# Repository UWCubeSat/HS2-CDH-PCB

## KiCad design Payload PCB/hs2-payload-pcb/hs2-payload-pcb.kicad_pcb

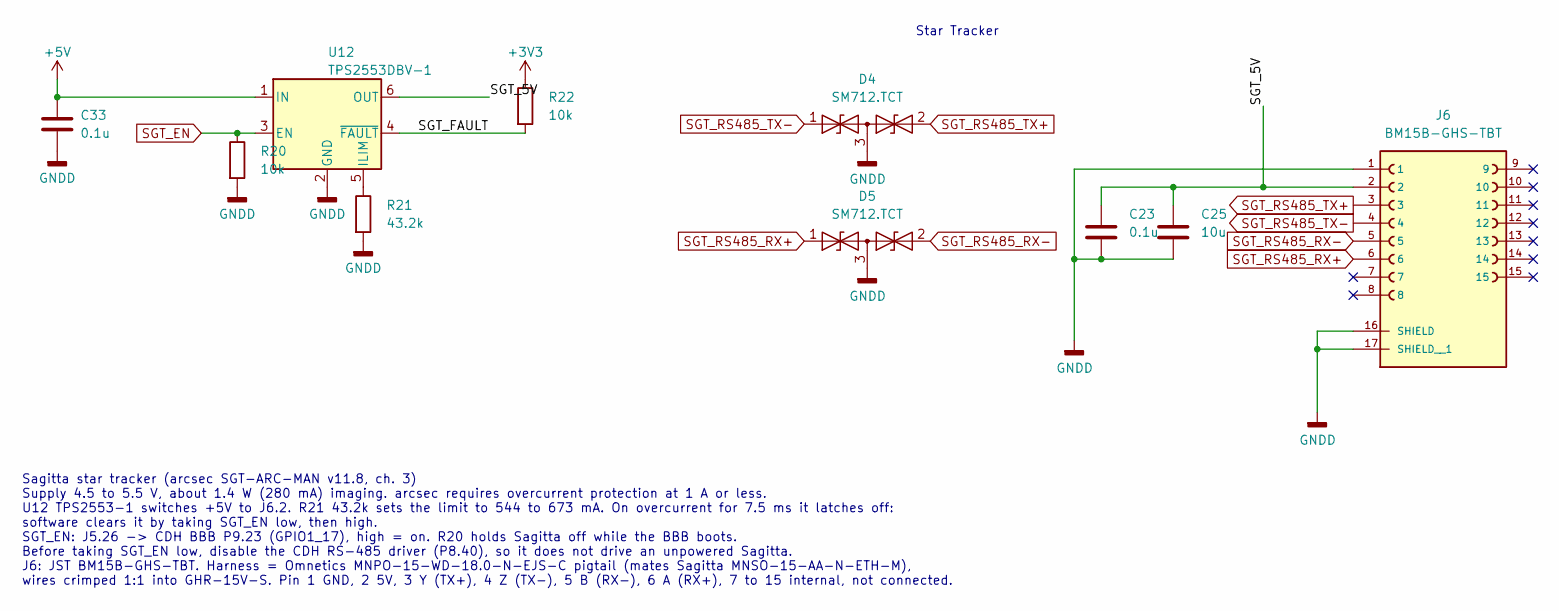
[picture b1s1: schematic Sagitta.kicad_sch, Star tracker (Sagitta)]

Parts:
C23, C33: 0.1u; C_0603_1608Metric
C25: 10u; C_0603_1608Metric
D4, D5: SM712.TCT; SOT-23; MPN SM712.TCT
J6: BM15B-GHS-TBT; BM15BGHSTBTLFSN; PARTREV B
R20, R22: 10k; R_0603_1608Metric
R21: 43.2k; R_0603_1608Metric
U12: TPS2553DBV-1; SOT-23-6; MPN TPS2553DBVR-1

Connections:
+3V3: R22.1; also elsewhere on the board
+5V: C33.1, U12.1 (IN); also elsewhere on the board
/Sagitta/SGT_5V: C23.1, C25.1, J6.2, U12.6 (OUT)
/Sagitta/SGT_FAULT: R22.2, U12.4 (~FAULT)
GNDD: C23.2, C25.2, C33.2, D4.3 (common), D5.3 (common), J6.1, J6.16 (SHIELD), J6.17 (SHIELD__1), R20.2, R21.2, U12.2 (GND); also elsewhere on the board
unnamed: R21.1, U12.5 (ILIM)
SGT_EN: R20.1, U12.3 (EN); also elsewhere on the board
SGT_RS485_RX+: D5.1 (A1), J6.6; also elsewhere on the board
SGT_RS485_RX-: D5.2 (A2), J6.5; also elsewhere on the board
SGT_RS485_TX+: D4.2 (A2), J6.3; also elsewhere on the board
SGT_RS485_TX-: D4.1 (A1), J6.4; also elsewhere on the board

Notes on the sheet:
Star Tracker
Sagitta star tracker (arcsec SGT-ARC-MAN v11.8, ch. 3) Supply 4.5 to 5.5 V, about 1.4 W (280 mA) imaging. arcsec requires overcurrent protection at 1 A or less. U12 TPS2553-1 switches +5V to J6.2. R21 43.2k sets the limit to 544 to 673 mA. On overcurrent for 7.5 ms it latches off: software clears i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

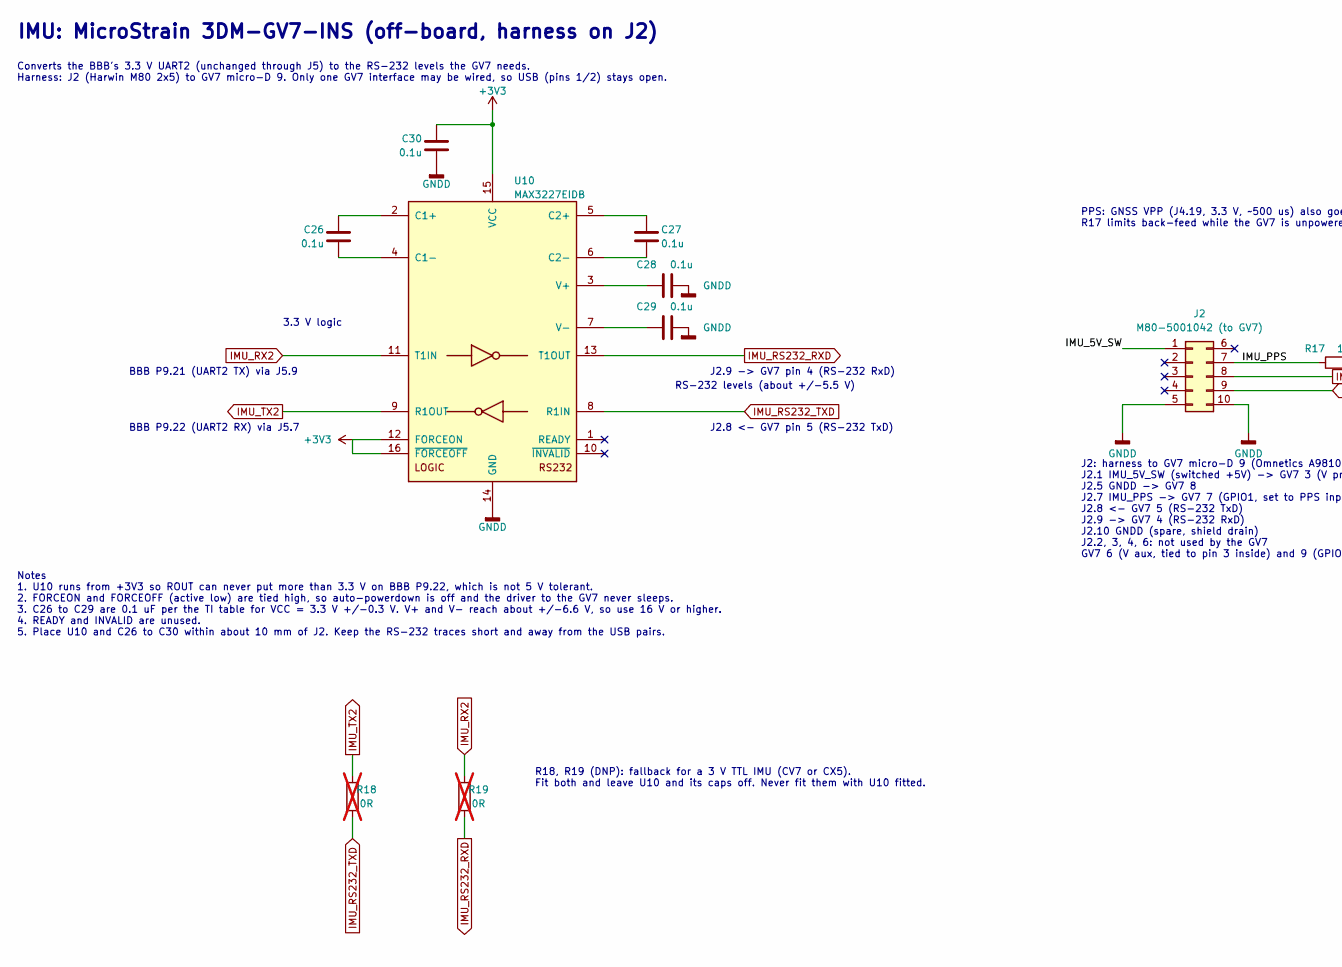
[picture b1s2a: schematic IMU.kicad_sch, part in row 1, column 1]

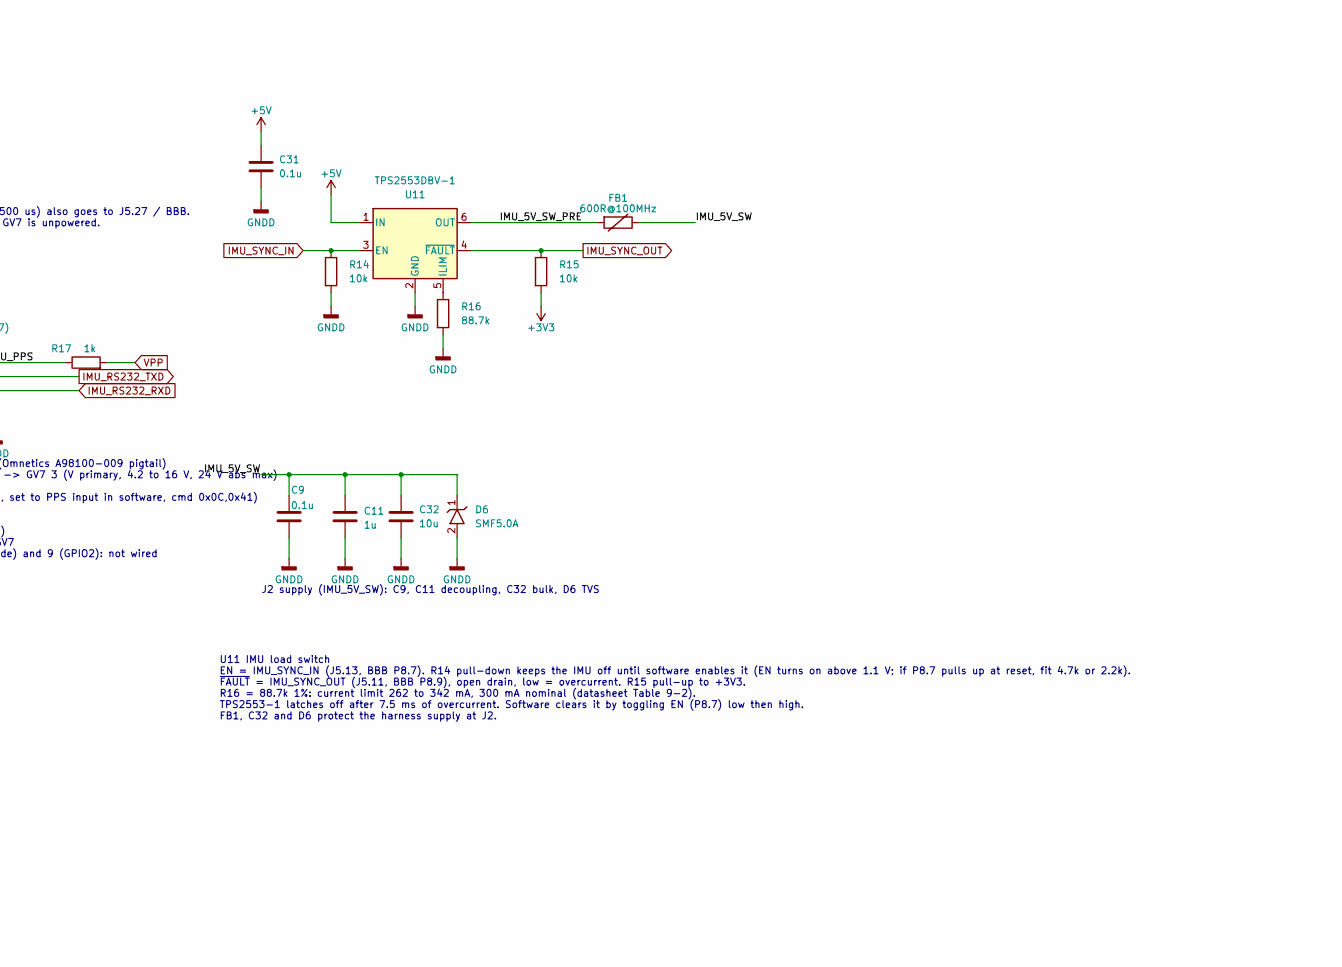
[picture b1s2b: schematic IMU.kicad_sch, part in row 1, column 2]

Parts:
C9, C26, C27, C28, C29, C30, C31: 0.1u; C_0603_1608Metric
C11: 1u; C_0603_1608Metric
C32: 10u; C_0805_2012Metric
D6: SMF5.0A; D_SMF; MPN SMF5.0A
FB1: 600R@100MHz; L_0805_2012Metric
J2: M80-5001042 (to GV7); Harwin-M80-5001042-0-0-MFG
R14, R15: 10k; R_0603_1608Metric
R16: 88.7k; R_0603_1608Metric
R17: 1k; R_0603_1608Metric
R18, R19: 0R; R_0402_1005Metric; not fitted
U10: MAX3227EIDB; SSOP-16_5.3x6.2mm_P0.65mm; MPN MAX3227EIDBR
U11: TPS2553DBV-1; SOT-23-6; MPN TPS2553DBVR-1

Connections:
+3V3: C30.1, R15.2, U10.12 (FORCEON), U10.15 (VCC), U10.16 (~FORCEOFF); also elsewhere on the board
+5V: C31.1, U11.1 (IN); also elsewhere on the board
/IMU/IMU_5V_SW: C9.1, C11.1, C32.1, D6.1 (K), FB1.2, J2.1
/IMU/IMU_5V_SW_PRE: FB1.1, U11.6 (OUT)
/IMU/IMU_PPS: J2.7, R17.1
GNDD: C9.2, C11.2, C28.2, C29.2, C30.2, C31.2, C32.2, D6.2 (A), J2.5, J2.10, R14.2, R16.2, U10.14 (GND), U11.2 (GND); also elsewhere on the board
IMU_RS232_RXD: J2.9, R19.2, U10.13 (T1OUT)
IMU_RS232_TXD: J2.8, R18.2, U10.8 (R1IN)
IMU_RX2: R19.1, U10.11 (T1IN); also elsewhere on the board
IMU_SYNC_IN: R14.1, U11.3 (EN); also elsewhere on the board
IMU_SYNC_OUT: R15.1, U11.4 (~FAULT); also elsewhere on the board
IMU_TX2: R18.1, U10.9 (R1OUT); also elsewhere on the board
unnamed: C26.1, U10.2 (C1+)
unnamed: C26.2, U10.4 (C1-)
unnamed: C27.1, U10.5 (C2+)
unnamed: C27.2, U10.6 (C2-)
unnamed: C28.1, U10.3 (V+)
unnamed: C29.1, U10.7 (V-)
unnamed: R16.1, U11.5 (ILIM)
VPP: R17.2; also elsewhere on the board

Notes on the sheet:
BBB P9.22 (UART2 RX) via J5.7
U11 IMU load switch EN = IMU_SYNC_IN (J5.13, BBB P8.7). R14 pull-down keeps the IMU off until software enables it (EN turns on above 1.1 V; if P8.7 pulls up at reset, fit 4.7k or 2.2k). ~{FAULT} = IMU_SYNC_OUT (J5.11, BBB P8.9), open drain, low = overcurrent. R15 pull-up to +3V3. R16 = 88.7k 1%: cu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
3.3 V logic
PPS: GNSS VPP (J4.19, 3.3 V, ~500 us) also goes to J5.27 / BBB. R17 limits back-feed while the GV7 is unpowered.
IMU: MicroStrain 3DM-GV7-INS (off-board, harness on J2)
Converts the BBB's 3.3 V UART2 (unchanged through J5) to the RS-232 levels the GV7 needs. Harness: J2 (Harwin M80 2x5) to GV7 micro-D 9. Only one GV7 interface may be wired, so USB (pins 1/2) stays open.
J2.8 <- GV7 pin 5 (RS-232 TxD)
Notes 1. U10 runs from +3V3 so ROUT can never put more than 3.3 V on BBB P9.22, which is not 5 V tolerant. 2. FORCEON and FORCEOFF (active low) are tied high, so auto-powerdown is off and the driver to the GV7 never sleeps. 3. C26 to C29 are 0.1 uF per the TI table for VCC = 3.3 V +/-0.3 V. V+ and 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
RS-232 levels (about +/-5.5 V)
BBB P9.21 (UART2 TX) via J5.9
J2 supply (IMU_5V_SW): C9, C11 decoupling, C32 bulk, D6 TVS
J2: harness to GV7 micro-D 9 (Omnetics A98100-009 pigtail) J2.1 IMU_5V_SW (switched +5V) -> GV7 3 (V primary, 4.2 to 16 V, 24 V abs max) J2.5 GNDD -> GV7 8 J2.7 IMU_PPS -> GV7 7 (GPIO1, set to PPS input in software, cmd 0x0C,0x41) J2.8 <- GV7 5 (RS-232 TxD) J2.9 -> GV7 4 (RS-232 RxD) J2.10 GNDD (sp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
R18, R19 (DNP): fallback for a 3 V TTL IMU (CV7 or CX5). Fit both and leave U10 and its caps off. Never fit them with U10 fitted.
J2.9 -> GV7 pin 4 (RS-232 RxD)

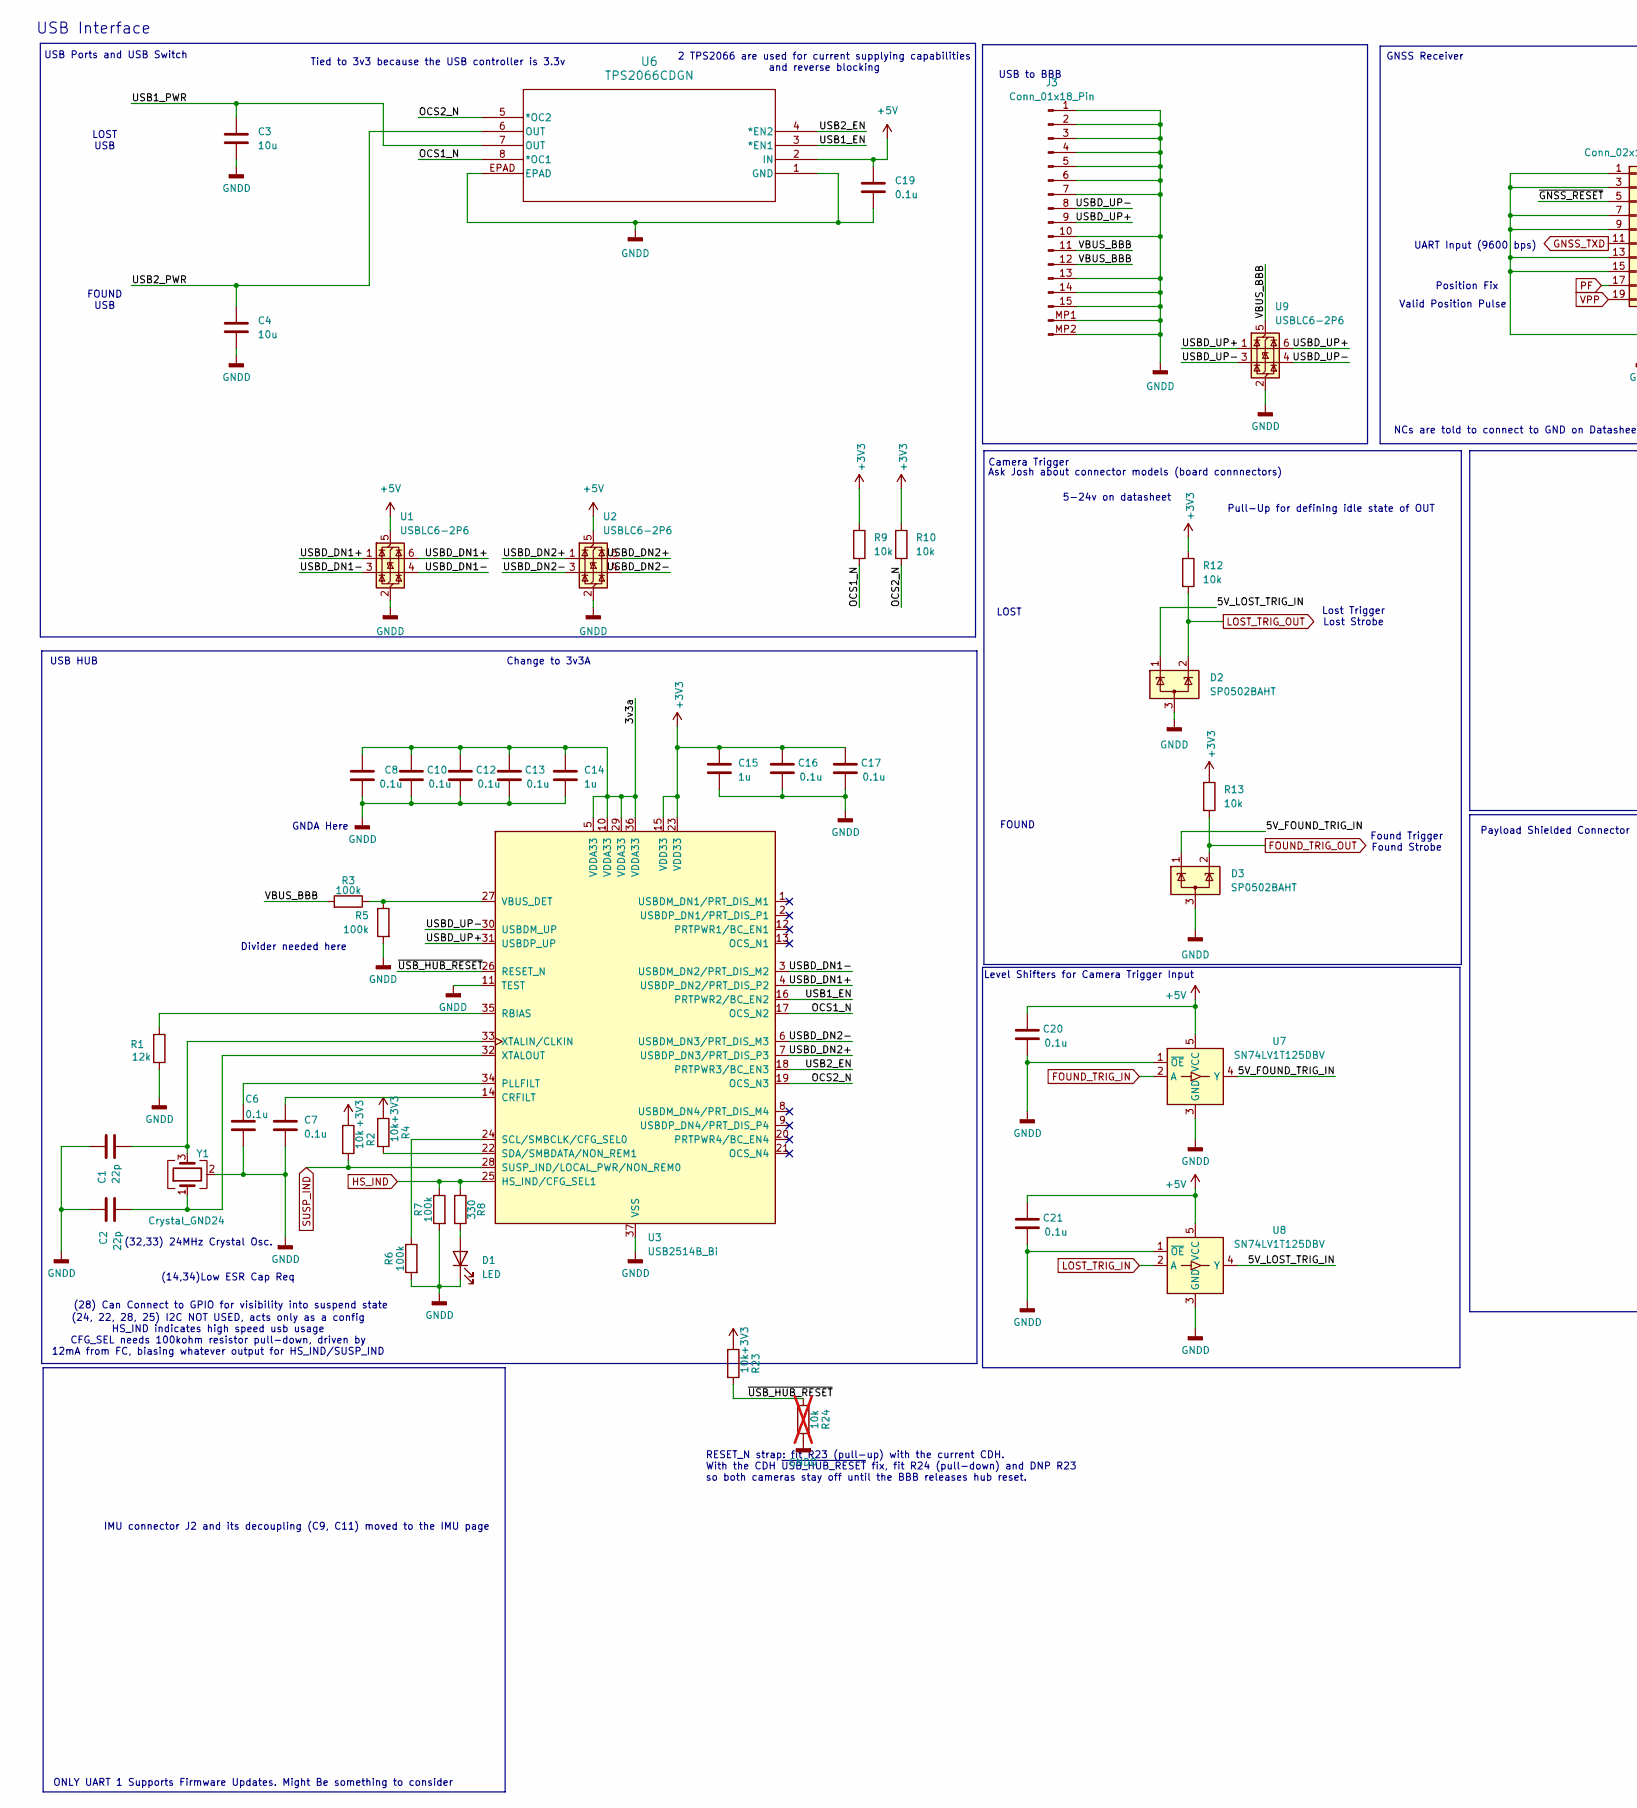
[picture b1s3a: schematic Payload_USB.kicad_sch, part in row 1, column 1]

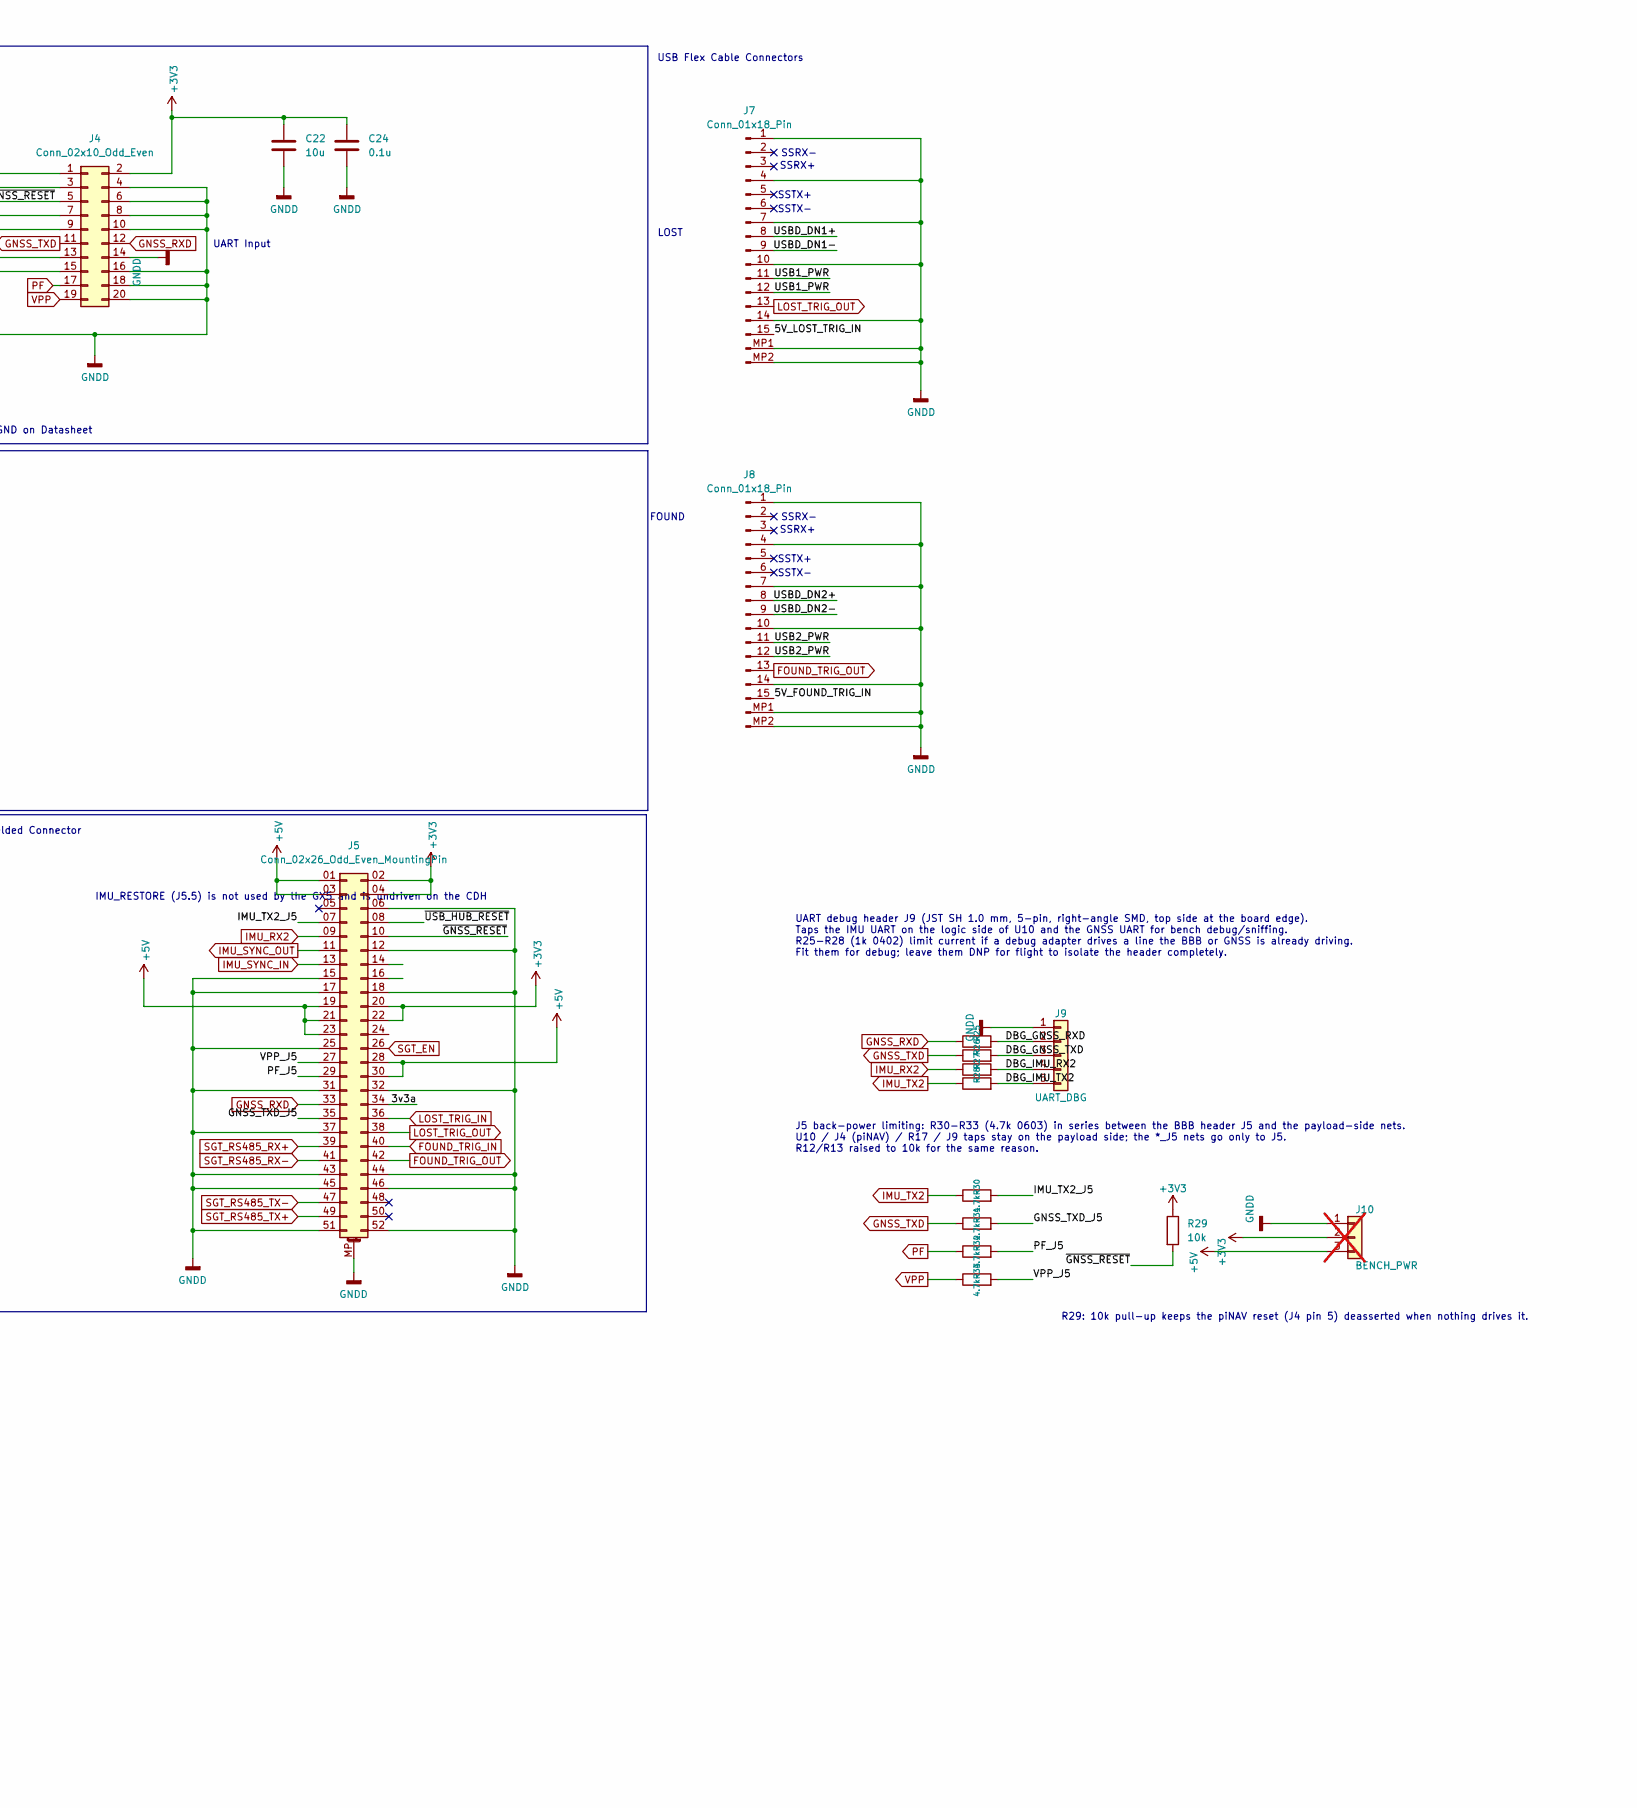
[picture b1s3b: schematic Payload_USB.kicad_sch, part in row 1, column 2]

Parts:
C1, C2: 22p; C_0603_1608Metric
C3, C4, C22: 10u; C_0603_1608Metric
C6, C7, C8, C10, C12, C13, C16, C17, C19, C20, C21, C24: 0.1u; C_0603_1608Metric
C14, C15: 1u; C_0603_1608Metric
D1: LED; LED_0603_1608Metric
D2, D3: SP0502BAHT; SOT-23
J3, J7, J8: Conn_01x18_Pin; Molex 502231-1500
J4: Conn_02x10_Odd_Even; PinHeader_2x10_P2.00mm_Vertical
J5: Conn_02x26_Odd_Even_MountingPin; SAMTEC_ASP-129646-01
J9: UART_DBG; JST_SH_SM05B-SRSS-TB_1x05-1MP_P1.00mm_Horizontal
J10: BENCH_PWR; PinHeader_1x03_P2.54mm_Horizontal; not fitted
R1: 12k; R_0603_1608Metric
R2, R4, R9, R10, R12, R13, R23, R29: 10k; R_0603_1608Metric
R3, R5, R6, R7: 100k; R_0603_1608Metric
R8: 330; R_0603_1608Metric
R24: 10k; R_0603_1608Metric; not fitted
R25, R26, R27, R28: 1k; R_0603_1608Metric
R30, R31, R32, R33: 4.7k; R_0603_1608Metric
U1, U2, U9: USBLC6-2P6; SOT-666
U3: USB2514B_Bi; QFN-36-1EP_6x6mm_P0.5mm_EP3.7x3.7mm
U6: TPS2066CDGN; DGN8_1P89x1P57_TEX
U7, U8: SN74LV1T125DBV; SOT-23-5
Y1: Crystal_GND24; Crystal_SMD_Abracon_ABM8G-4Pin_3.2x2.5mm

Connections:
+3V3: C15.1, C16.1, C17.1, C22.1, C24.1, J4.2, J5.02 (Pin_2), J5.04 (Pin_4), J5.20, J5.22, J10.2, R2.1, R4.1, R9.1, R10.1, R12.1, R13.1, R23.1, R29.1, U3.15 (VDD33), U3.23 (VDD33); also elsewhere on the board
+5V: C19.1, C20.1, C21.1, J5.01 (Pin_1), J5.03 (Pin_3), J5.19, J5.21, J5.23, J5.28, J5.30, J10.3, U1.5 (VBUS), U2.5 (VBUS), U6.2 (IN), U7.5 (VCC), U8.5 (VCC); also elsewhere on the board
/Payload_USB/3v3a: C8.1, C10.1, C12.1, C13.1, C14.1, J5.34, U3.5 (VDDA33), U3.10 (VDDA33), U3.29 (VDDA33), U3.36 (VDDA33)
/Payload_USB/5V_FOUND_TRIG_IN: D3.1 (K), J8.15, U7.4 (Y)
/Payload_USB/5V_LOST_TRIG_IN: D2.1 (K), J7.15, U8.4 (Y)
/Payload_USB/DBG_GNSS_RXD: J9.2, R25.2
/Payload_USB/DBG_GNSS_TXD: J9.3, R26.2
/Payload_USB/DBG_IMU_RX2: J9.4, R27.2
/Payload_USB/DBG_IMU_TX2: J9.5, R28.2
/Payload_USB/GNSS_TXD_J5: J5.35, R31.2
/Payload_USB/IMU_TX2_J5: J5.07 (Pin_7), R30.2
/Payload_USB/OCS1_N: R9.2, U3.17 (OCS_N2), U6.8 (*OC1)
/Payload_USB/OCS2_N: R10.2, U3.19 (OCS_N3), U6.5 (*OC2)
/Payload_USB/PF_J5: J5.29, R32.2
/Payload_USB/USB1_EN: U3.16 (PRTPWR2/BC_EN2), U6.3 (*EN1)
/Payload_USB/USB1_PWR: C3.1, J7.11, J7.12, U6.7 (OUT)
/Payload_USB/USB2_EN: U3.18 (PRTPWR3/BC_EN3), U6.4 (*EN2)
/Payload_USB/USB2_PWR: C4.1, J8.11, J8.12, U6.6 (OUT)
/Payload_USB/USBD_DN1+: J7.8, U1.1 (I/O1), U1.6 (I/O1), U3.4 (USBDP_DN2/PRT_DIS_P2)
/Payload_USB/USBD_DN1-: J7.9, U1.3 (I/O2), U1.4 (I/O2), U3.3 (USBDM_DN2/PRT_DIS_M2)
/Payload_USB/USBD_DN2+: J8.8, U2.1 (I/O1), U2.6 (I/O1), U3.7 (USBDP_DN3/PRT_DIS_P3)
/Payload_USB/USBD_DN2-: J8.9, U2.3 (I/O2), U2.4 (I/O2), U3.6 (USBDM_DN3/PRT_DIS_M3)
/Payload_USB/USBD_UP+: J3.9, U3.31 (USBDP_UP), U9.1 (I/O1), U9.6 (I/O1)
/Payload_USB/USBD_UP-: J3.8, U3.30 (USBDM_UP), U9.3 (I/O2), U9.4 (I/O2)
/Payload_USB/VBUS_BBB: J3.11, J3.12, R3.2, U9.5 (VBUS)
/Payload_USB/VPP_J5: J5.27, R33.2
/Payload_USB/~GNSS_RESET: J4.5, J5.10, R29.2
/Payload_USB/~USB_HUB_RESET: J5.08 (Pin_8), R23.2, R24.1, U3.26 (RESET_N)
FOUND_TRIG_IN: J5.40, U7.2 (A)
FOUND_TRIG_OUT: D3.2 (K), J5.42, J8.13, R13.2
GNDD: C1.1, C2.1, C3.2, C4.2, C6.2, C7.2, C8.2, C10.2, C12.2, C13.2, C14.2, C15.2, C16.2, C17.2, C19.2, C20.2, C21.2, C22.2, C24.2, D1.1 (K), D2.3 (A), D3.3 (A), J3.1, J3.2, J3.3, J3.4, J3.5, J3.6, J3.7, J3.10, J3.13, J3.14, J3.15, J3.MP1, J3.MP2, J4.1, J4.3, J4.4, J4.6, J4.7, J4.8, J4.9, J4.10, J4.13, J4.14, J4.15, J4.16, J4.18, J4.20, J5.06 (Pin_6), J5.12, J5.15, J5.17, J5.18, J5.25, J5.31, J5.32, J5.37, J5.43, J5.44, J5.45, J5.46, J5.51, J5.52, J5.MP (MountPin), J7.1, J7.4, J7.7, J7.10, J7.14, J7.MP1, J7.MP2, J8.1, J8.4, J8.7, J8.10, J8.14, J8.MP1, J8.MP2, J9.1, J10.1, R1.2, R5.2, R6.2, R7.2, R24.2, U1.2 (GND), U2.2 (GND), U3.11 (TEST), U3.37 (VSS), U6.1 (GND), U6.EPAD, U7.1 (~OE), U7.3 (GND), U8.1 (~OE), U8.3 (GND), U9.2 (GND), Y1.2 (G), Y1.4 (G); also elsewhere on the board
GNSS_RXD: J4.12, J5.33, R25.1
GNSS_TXD: J4.11, R26.1, R31.1
HS_IND: R7.1, R8.1, U3.25 (HS_IND/CFG_SEL1)
IMU_RX2: J5.09 (Pin_9), R27.1; also elsewhere on the board
IMU_SYNC_IN: J5.13; also elsewhere on the board
IMU_SYNC_OUT: J5.11; also elsewhere on the board
IMU_TX2: R28.1, R30.1; also elsewhere on the board
LOST_TRIG_IN: J5.36, U8.2 (A)
LOST_TRIG_OUT: D2.2 (K), J5.38, J7.13, R12.2
unnamed: D1.2 (A), R8.2
unnamed: C7.1, U3.14 (CRFILT)
unnamed: C6.1, U3.34 (PLLFILT)
unnamed: R1.1, U3.35 (RBIAS)
unnamed: R6.1, U3.24 (SCL/SMBCLK/CFG_SEL0)
unnamed: R4.2, U3.22 (SDA/SMBDATA/NON_REM1)
unnamed: R3.1, R5.1, U3.27 (VBUS_DET)
unnamed: C1.2, U3.33 (XTALIN/CLKIN), Y1.3
unnamed: C2.2, U3.32 (XTALOUT), Y1.1
PF: J4.17, R32.1
SGT_EN: J5.26; also elsewhere on the board
SGT_RS485_RX+: J5.39; also elsewhere on the board
SGT_RS485_RX-: J5.41; also elsewhere on the board
SGT_RS485_TX+: J5.49; also elsewhere on the board
SGT_RS485_TX-: J5.47; also elsewhere on the board
SUSP_IND: R2.2, U3.28 (SUSP_IND/LOCAL_PWR/NON_REM0)
VPP: J4.19, R33.1; also elsewhere on the board

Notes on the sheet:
USB Flex Cable Connectors
LOST USB
SSRX-
Level Shifters for Camera Trigger Input
SSTX-
Camera Trigger
GNDA Here
Change to 3v3A
FOUND USB
Divider needed here
(32,33) 24MHz Crystal Osc.
UART Input
Tied to 3v3 because the USB controller is 3.3v
NCs are told to connect to GND on Datasheet
LOST
SSTX+
ONLY UART 1 Supports Firmware Updates. Might Be something to consider
IMU connector J2 and its decoupling (C9, C11) moved to the IMU page
Pull-Up for defining idle state of OUT
IMU_RESTORE (J5.5) is not used by the GX5 and is undriven on the CDH
Found Trigger Found Strobe
SSRX+
GNSS Receiver
Payload Shielded Connector
(28) Can Connect to GPIO for visibility into suspend state
USB Ports and USB Switch
Position Fix
R29: 10k pull-up keeps the piNAV reset (J4 pin 5) deasserted when nothing drives it.
Ask Josh about connector models (board connnectors)
UART debug header J9 (JST SH 1.0 mm, 5-pin, right-angle SMD, top side at the board edge). Taps the IMU UART on the logic side of U10 and the GNSS UART for bench debug/sniffing. R25-R28 (1k 0402) limit current if a debug adapter drives a line the BBB or GNSS is already driving. Fit them for debug; l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
(24, 22, 28, 25) I2C NOT USED, acts only as a config HS_IND indicates high speed usb usage CFG_SEL needs 100kohm resistor pull-down, driven by 12mA from FC, biasing whatever output for HS_IND/SUSP_IND
Lost Trigger Lost Strobe
FOUND
USB HUB
J5 back-power limiting: R30-R33 (4.7k 0603) in series between the BBB header J5 and the payload-side nets. U10 / J4 (piNAV) / R17 / J9 taps stay on the payload side; the *_J5 nets go only to J5. R12/R13 raised to 10k for the same reason.
Valid Position Pulse
5-24v on datasheet
USB Interface
LOST
USB to BBB

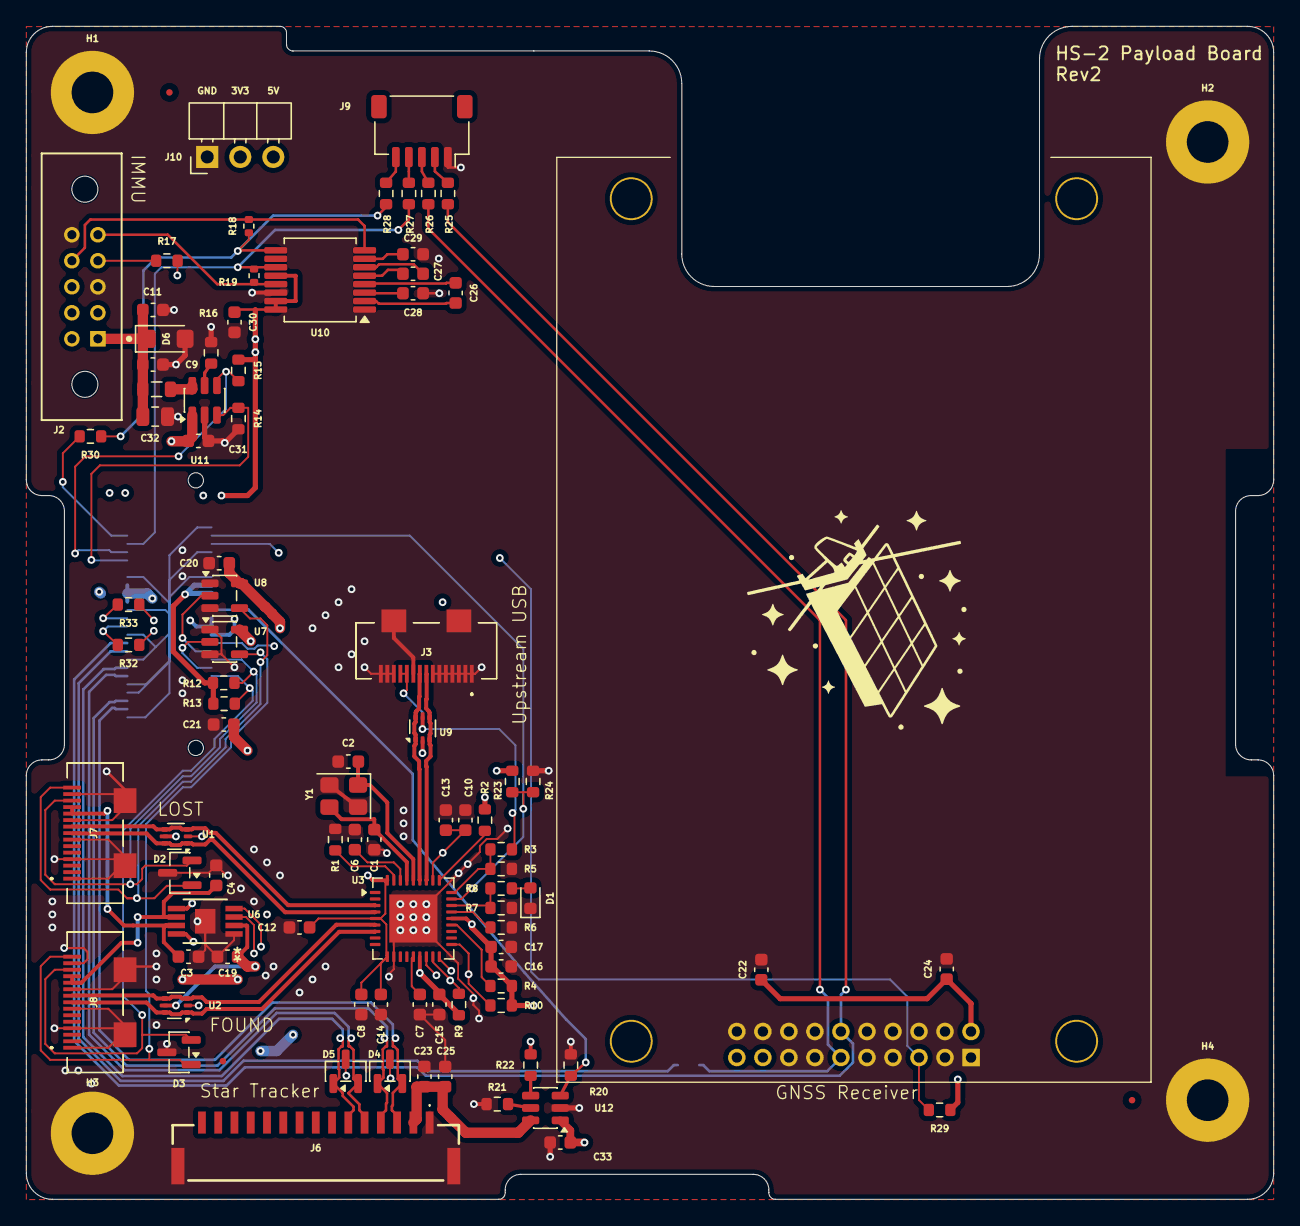
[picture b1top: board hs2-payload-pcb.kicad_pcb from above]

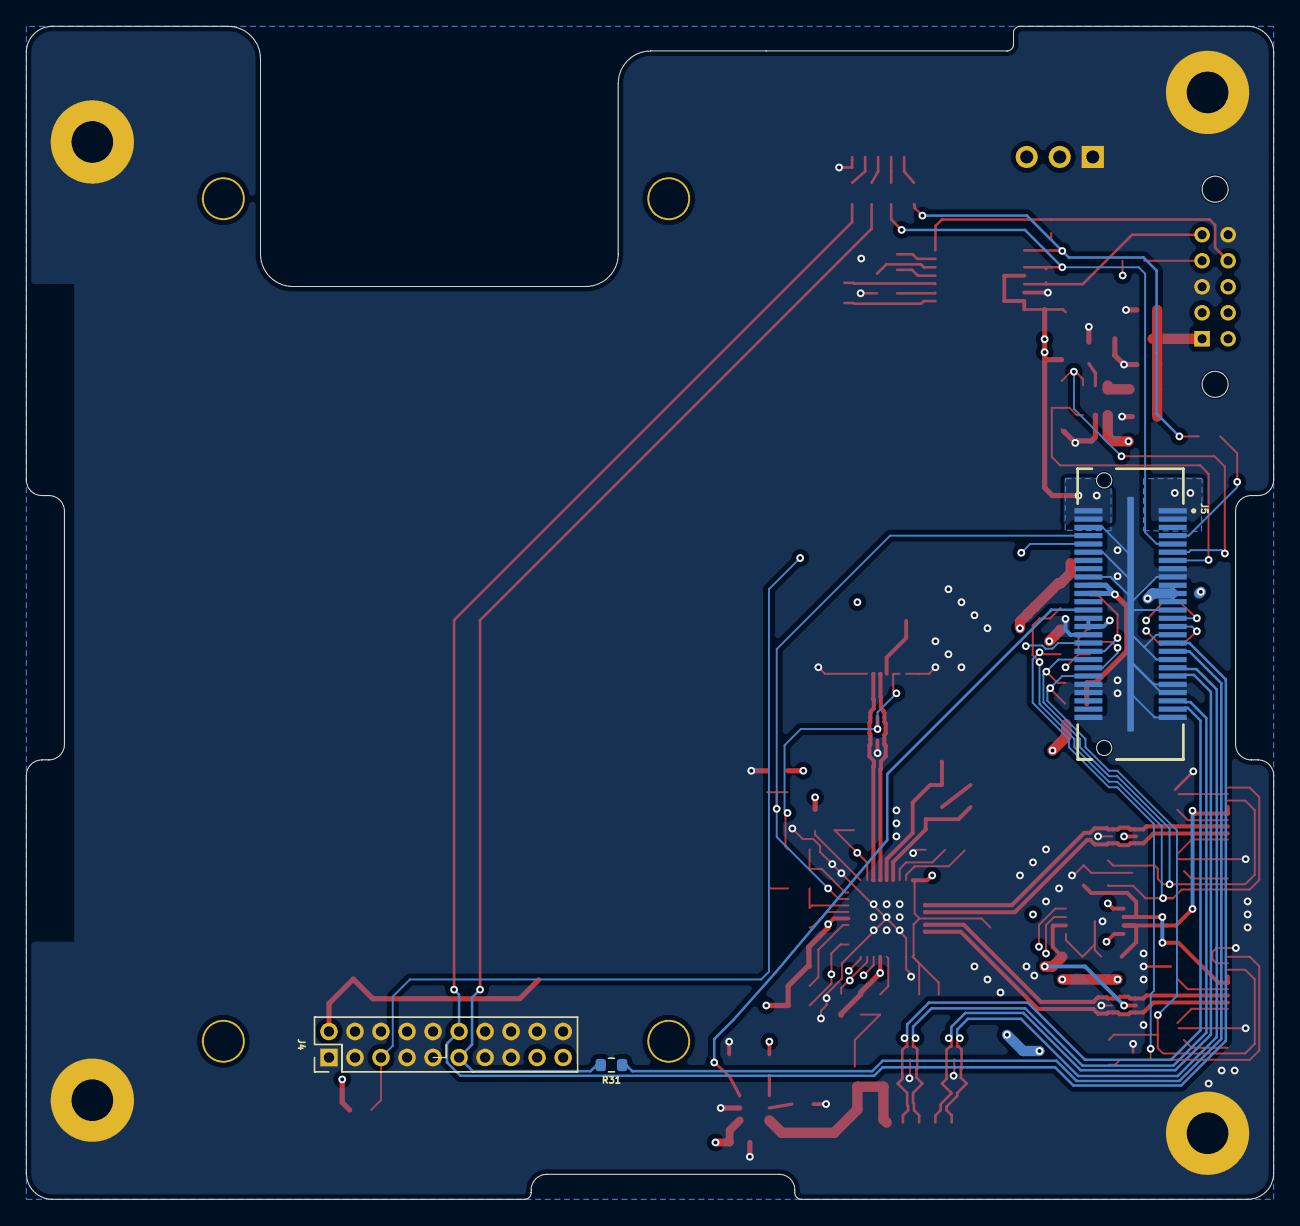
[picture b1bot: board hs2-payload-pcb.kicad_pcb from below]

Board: 4 copper layers, 95.9 x 90.2 mm, 94 parts (3 on the bottom side), 72 nets.

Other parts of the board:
H1, H2, H3, H4: MountingHole_Pad; MountingHole_3.2mm_M3_Pad

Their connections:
GNDD: H1.1 (1_1), H2.1 (1_1), H3.1 (1_1), H4.1 (1_1); also elsewhere on the board

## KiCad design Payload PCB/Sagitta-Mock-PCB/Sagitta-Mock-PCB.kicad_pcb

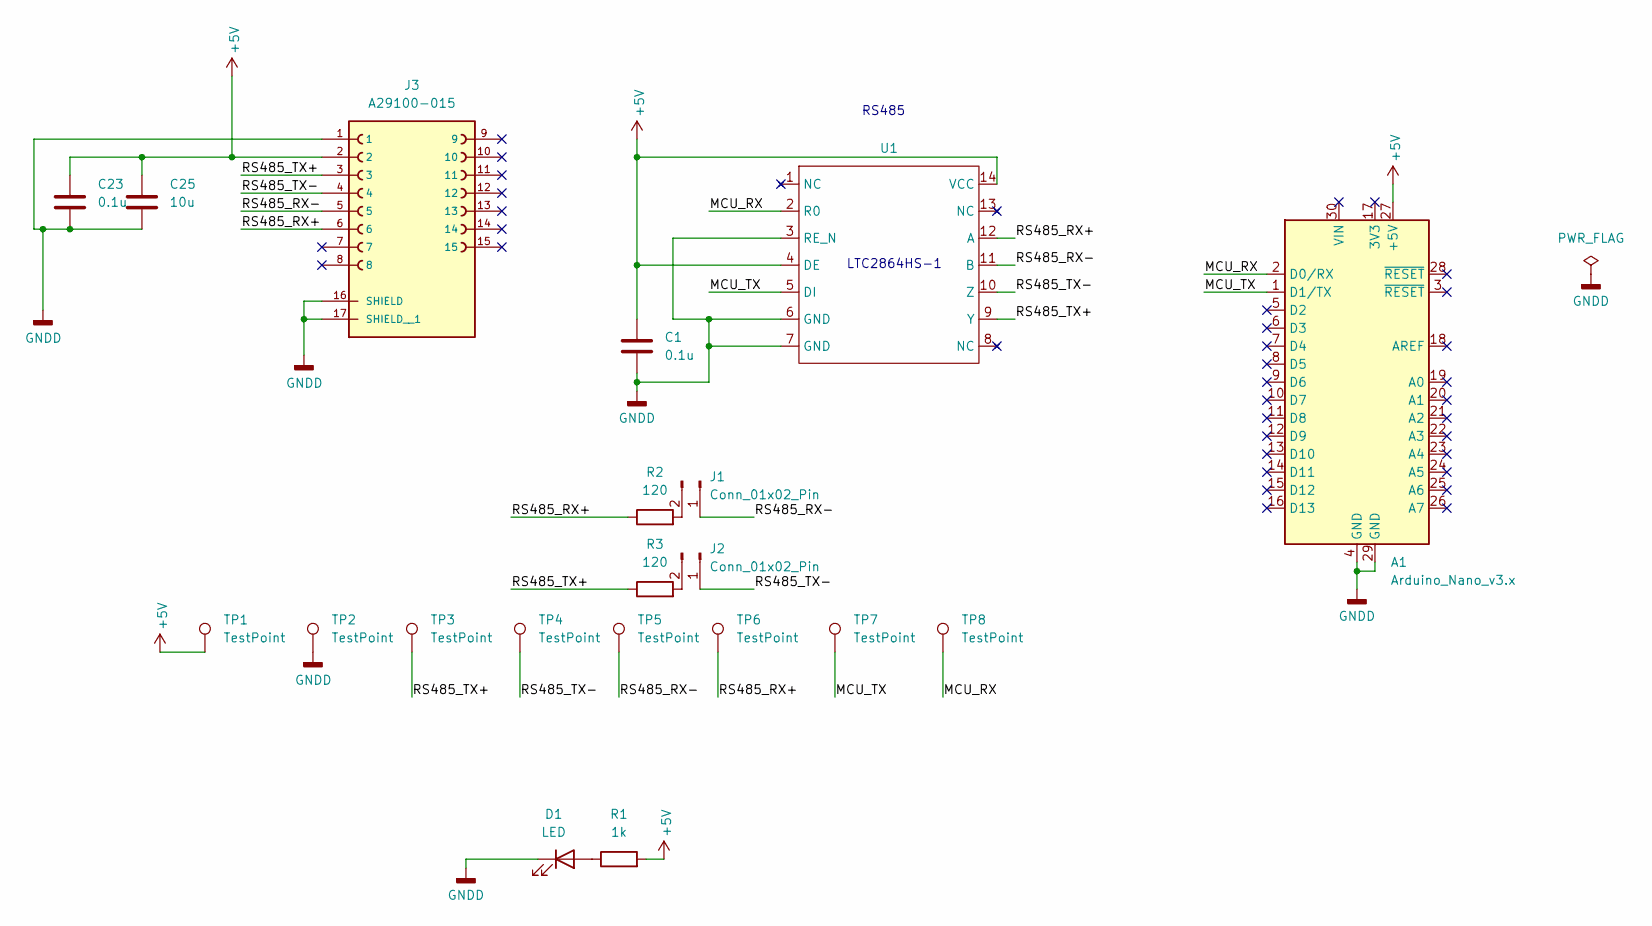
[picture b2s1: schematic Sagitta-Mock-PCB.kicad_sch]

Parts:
A1: Arduino_Nano_v3.x; Arduino_Nano
C1, C23: 0.1u; C_0603_1608Metric
C25: 10u; C_0603_1608Metric
D1: LED; LED_0603_1608Metric
J1, J2: Conn_01x02_Pin; PinHeader_1x02_P2.54mm_Vertical
J3: A29100-015; CONN_BM15B-GHS-TBT_JST; PARTREV B
R1: 1k; R_0603_1608Metric
R2, R3: 120; R_0603_1608Metric
TP1, TP2, TP3, TP4, TP5, TP6, TP7, TP8: TestPoint; TestPoint_Pad_1.0x1.0mm
U1: SOIC-14_3.9x8.7mm_P1.27mm

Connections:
+5V: A1.27 (+5V), C1.1, C23.1, C25.1, J3.2, R1.2, TP1.1 (1_1), U1.4 (DE), U1.14 (VCC)
/MCU_RX: A1.2 (D0/RX), TP8.1 (1_1), U1.2 (R0)
/MCU_TX: A1.1 (D1/TX), TP7.1 (1_1), U1.5 (DI)
/RS485_RX+: J3.6, R2.1, TP6.1 (1_1), U1.12 (A)
/RS485_RX-: J1.1, J3.5, TP5.1 (1_1), U1.11 (B)
/RS485_TX+: J3.3, R3.1, TP3.1 (1_1), U1.9 (Y)
/RS485_TX-: J2.1, J3.4, TP4.1 (1_1), U1.10 (Z)
GNDD: A1.4 (GND), A1.29 (GND), C1.2, C23.2, C25.2, D1.1 (K), J3.1, J3.16 (SHIELD), J3.17 (SHIELD__1), TP2.1 (1_1), U1.3 (RE_N), U1.6 (GND), U1.7 (GND)
unnamed: D1.2 (A), R1.1
unnamed: J1.2, R2.2
unnamed: J2.2, R3.2

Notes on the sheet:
RS485
LTC2864HS-1

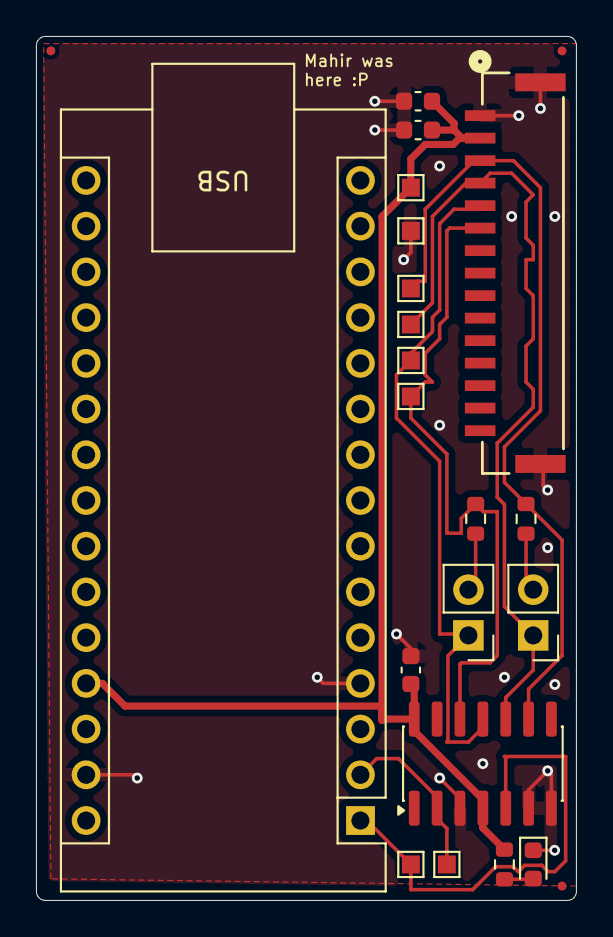
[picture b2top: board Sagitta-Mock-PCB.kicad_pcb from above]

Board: 2 copper layers, 30.0 x 48.0 mm, 20 parts (0 on the bottom side), 11 nets.

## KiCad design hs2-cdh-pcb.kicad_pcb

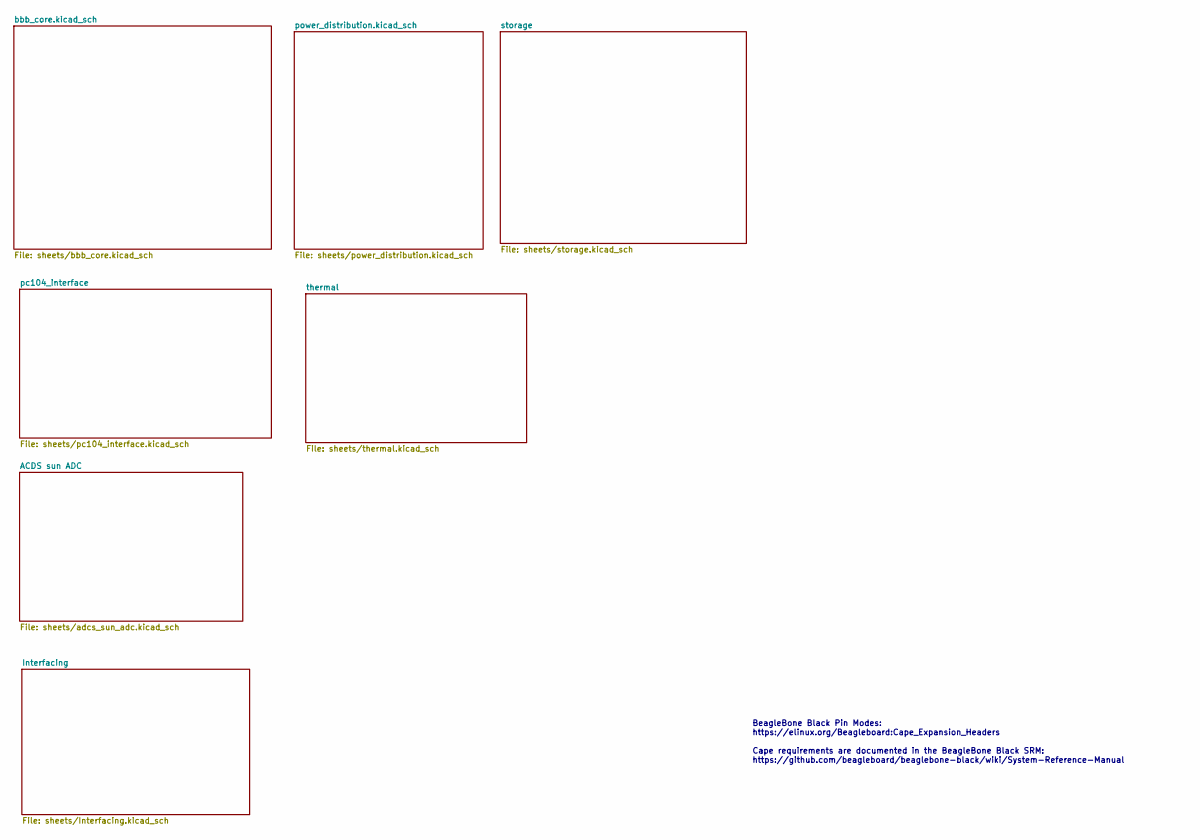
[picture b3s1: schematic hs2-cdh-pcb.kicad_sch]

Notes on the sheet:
BeagleBone Black Pin Modes: https://elinux.org/Beagleboard:Cape_Expansion_Headers Cape requirements are documented in the BeagleBone Black SRM: https://github.com/beagleboard/beaglebone-black/wiki/System-Reference-Manual
